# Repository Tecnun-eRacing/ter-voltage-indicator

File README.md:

# Ter Voltage Indicator
Voltage Indicator PCB designed for formula student. It enables at ~25V and can be increased if needded.
It is designed around a buck converter and should be able to power more logic if needed.

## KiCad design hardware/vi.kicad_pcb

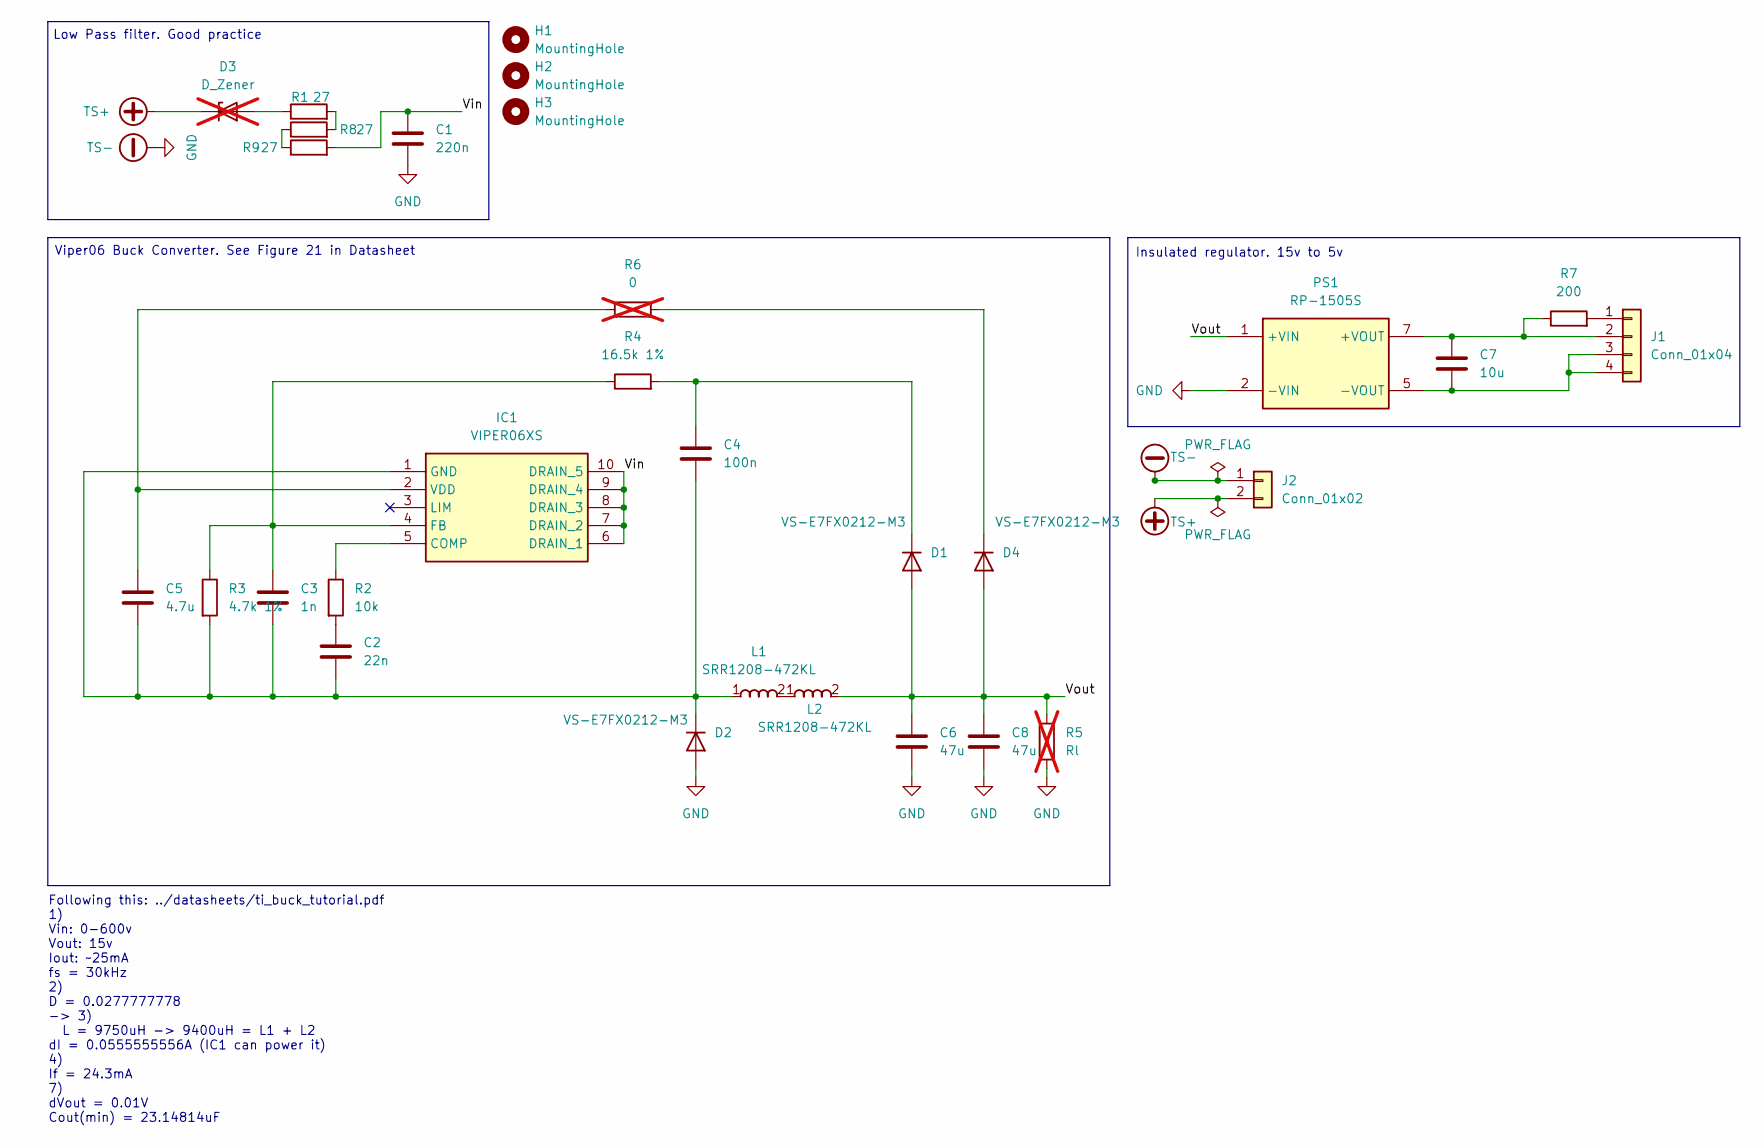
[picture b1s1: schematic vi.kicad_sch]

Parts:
C1: 220n; C_2220_5750Metric_Pad1.97x5.40mm_HandSolder
C2: 22n; C_0603_1608Metric_Pad1.08x0.95mm_HandSolder
C3: 1n; C_0603_1608Metric_Pad1.08x0.95mm_HandSolder
C4: 100n; C_0603_1608Metric_Pad1.08x0.95mm_HandSolder
C5: 4.7u; C_0603_1608Metric_Pad1.08x0.95mm_HandSolder
C6, C8: 47u; C_1210_3225Metric_Pad1.33x2.70mm_HandSolder
C7: 10u; C_0603_1608Metric_Pad1.08x0.95mm_HandSolder
D1, D2, D4: VS-E7FX0212-M3; D_SMF
D3: D_Zener; D_SOD-123; not fitted
H1, H2, H3: MountingHole; MountingHole_2.2mm_M2
IC1: VIPER06XS; SOP100P600X175-10N; Mouser Part Number 511-VIPER06XS
J1: Conn_01x04; Molex_Micro-Fit_3.0_43650-0415_1x04_P3.00mm_Vertical
J2: Conn_01x02; Molex_Micro-Fit_3.0_43650-0215_1x02_P3.00mm_Vertical
L1, L2: SRR1208-472KL; SRR1208; Mouser Part Number 652-SRR1208-472KL
PS1: RP-1505S; RP1505S; Mouser Part Number 919-RP-1505S
R1, R8, R9: 27; R_1206_3216Metric_Pad1.30x1.75mm_HandSolder
R2: 10k; R_0603_1608Metric_Pad0.98x0.95mm_HandSolder
R3: 4.7k 1%; R_0603_1608Metric_Pad0.98x0.95mm_HandSolder
R4: 16.5k 1%; R_0603_1608Metric_Pad0.98x0.95mm_HandSolder
R5: Rl; R_0603_1608Metric_Pad0.98x0.95mm_HandSolder; not fitted
R6: 0; R_0603_1608Metric_Pad0.98x0.95mm_HandSolder; not fitted
R7: 200; R_0603_1608Metric_Pad0.98x0.95mm_HandSolder

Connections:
/Vin: C1.1, IC1.6 (DRAIN_1), IC1.7 (DRAIN_2), IC1.8 (DRAIN_3), IC1.9 (DRAIN_4), IC1.10 (DRAIN_5), R9.2
/Vout: C6.1, C8.1, D1.2 (A), D4.2 (A), L2.2, PS1.1 (+VIN), R5.1
GND: C1.2, C6.2, C8.2, D2.2 (A), J2.1, PS1.2 (-VIN), R5.2
unnamed: C2.1, R2.2
unnamed: C4.1, D1.1 (K), R4.2
unnamed: C2.2, C3.2, C4.2, C5.2, D2.1 (K), IC1.1 (GND), L1.1, R3.2
unnamed: D3.2 (A), R1.1
unnamed: D4.1 (K), R6.2
unnamed: IC1.5 (COMP), R2.1
unnamed: C3.1, IC1.4 (FB), R3.1, R4.1
unnamed: C5.1, IC1.2 (VDD), R6.1
unnamed: J1.1, R7.2
unnamed: C7.1, J1.2, PS1.7 (+VOUT), R7.1
unnamed: C7.2, J1.3, J1.4, PS1.5 (-VOUT)
unnamed: L1.2, L2.1
unnamed: R1.2, R8.2
unnamed: R8.1, R9.1
TS+: D3.1 (K), J2.2

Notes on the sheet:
Low Pass filter. Good practice
Following this: ../datasheets/ti_buck_tutorial.pdf 1) Vin: 0-600v Vout: 15v Iout: ~25mA fs = 30kHz 2) D = 0.0277777778 -> 3) L = 9750uH -> 9400uH = L1 + L2 dI = 0.0555555556A (IC1 can power it) 4) If = 24.3mA 7) dVout = 0.01V Cout(min) = 23.14814uF
Viper06 Buck Converter. See Figure 21 in Datasheet
Insulated regulator. 15v to 5v

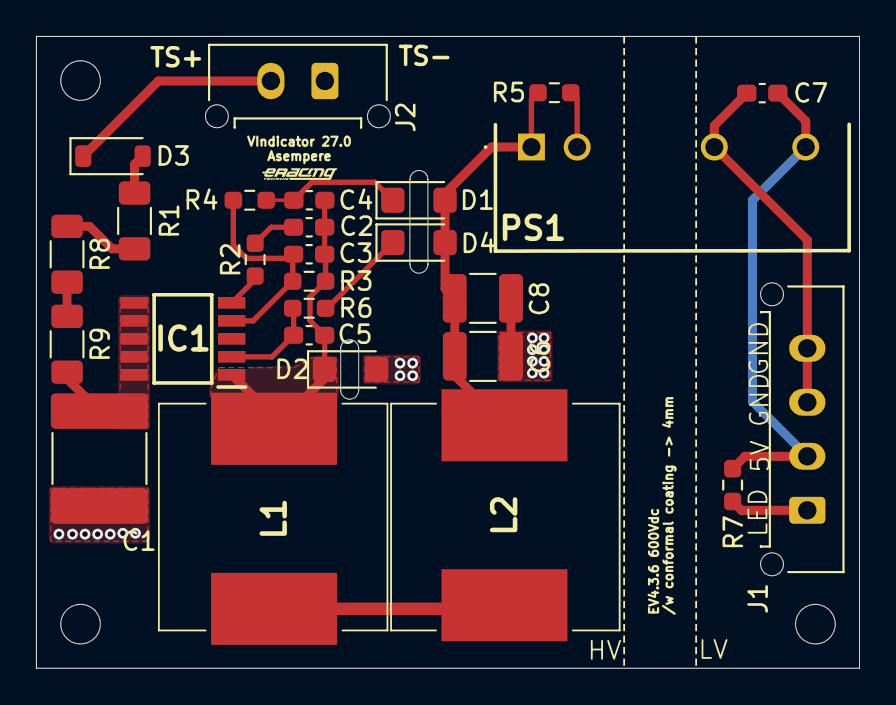
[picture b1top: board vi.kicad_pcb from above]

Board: 2 copper layers, 45.7 x 35.1 mm, 30 parts (0 on the bottom side), 18 nets.
